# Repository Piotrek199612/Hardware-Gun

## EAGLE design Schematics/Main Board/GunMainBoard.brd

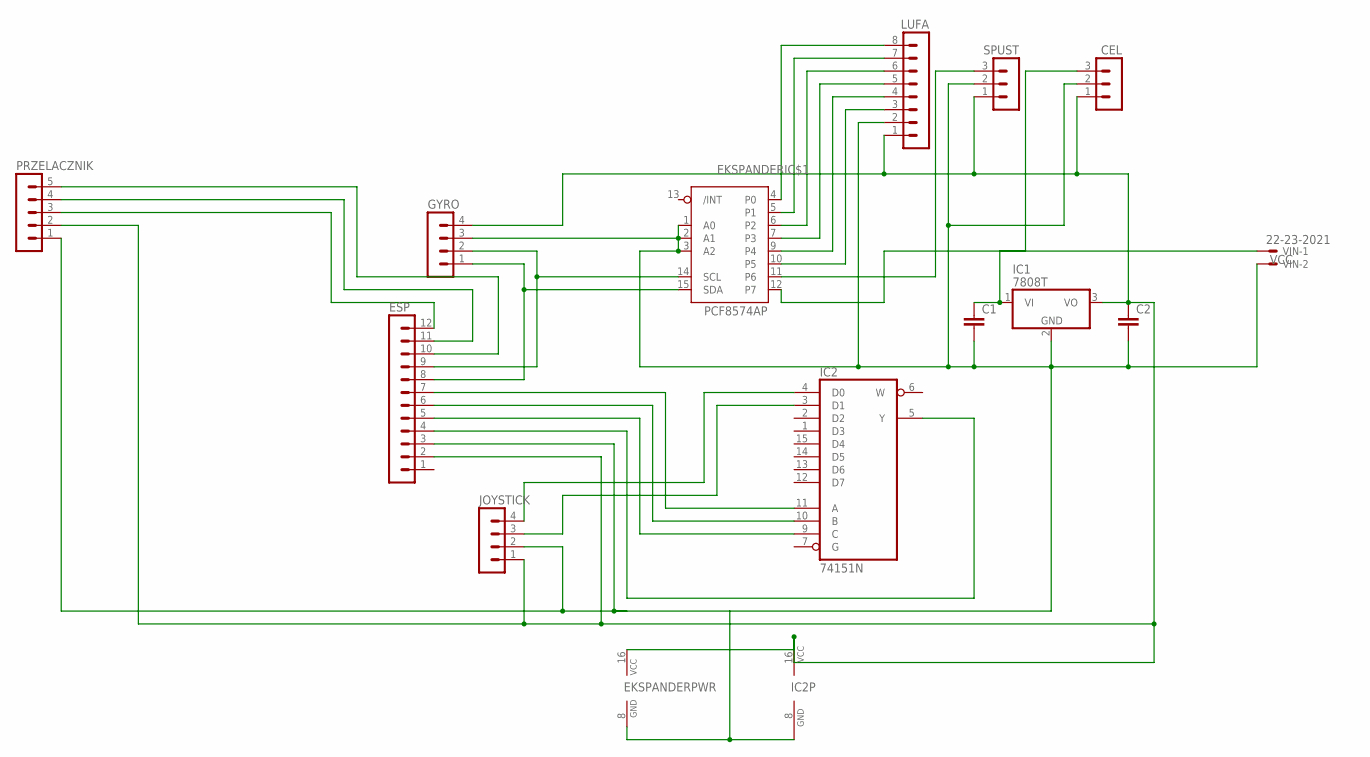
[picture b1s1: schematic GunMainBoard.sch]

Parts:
C1, C2: C-EU025-024X044; C025-024X044
CEL: MA03-1
EKSPANDER: PCF8574AP; DIL16
ESP: MA12-1
GYRO: MA04-1
IC1: 7808T; TO220H
IC2: 74151N; DIL16
JOYSTICK: MA04-1
LUFA: MA08-1
PRZELACZNIK: MA05-1
SPUST: MA03-1
VIN: 22-23-2021

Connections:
unnamed: ESP.10, PRZELACZNIK.5
unnamed: EKSPANDER.15 (SDA), ESP.8, GYRO.1
unnamed: EKSPANDER.4 (P0), LUFA.8
unnamed: ESP.7, IC2.11 (A)
unnamed: EKSPANDER.14 (SCL), ESP.9, GYRO.2
unnamed: ESP.6, IC2.10 (B)
unnamed: ESP.5, IC2.9 (C)
unnamed: ESP.4, IC2.5 (Y)
unnamed: C1.2, C2.2, CEL.2, EKSPANDER.1 (A0), EKSPANDER.2 (A1), EKSPANDER.3 (A2), EKSPANDER.8 (GND), ESP.3, GYRO.3, IC1.2 (GND), IC2.8 (GND), JOYSTICK.2, LUFA.2, PRZELACZNIK.1, SPUST.2, VIN.2
unnamed: EKSPANDER.5 (P1), LUFA.7
unnamed: EKSPANDER.6 (P2), LUFA.6
unnamed: EKSPANDER.7 (P3), LUFA.5
unnamed: EKSPANDER.9 (P4), LUFA.4
unnamed: EKSPANDER.10 (P5), LUFA.3
unnamed: EKSPANDER.11 (P6), SPUST.3
unnamed: C1.1, IC1.1 (VI), VIN.1
unnamed: IC2.3 (D1), JOYSTICK.3
unnamed: CEL.3, EKSPANDER.12 (P7)
unnamed: IC2.4 (D0), JOYSTICK.4
unnamed: ESP.11, PRZELACZNIK.4
unnamed: ESP.12, PRZELACZNIK.3
unnamed: C2.1, CEL.1, EKSPANDER.16 (VCC), ESP.2, GYRO.4, IC1.3 (VO), IC2.16 (VCC), JOYSTICK.1, LUFA.1, PRZELACZNIK.2, SPUST.1

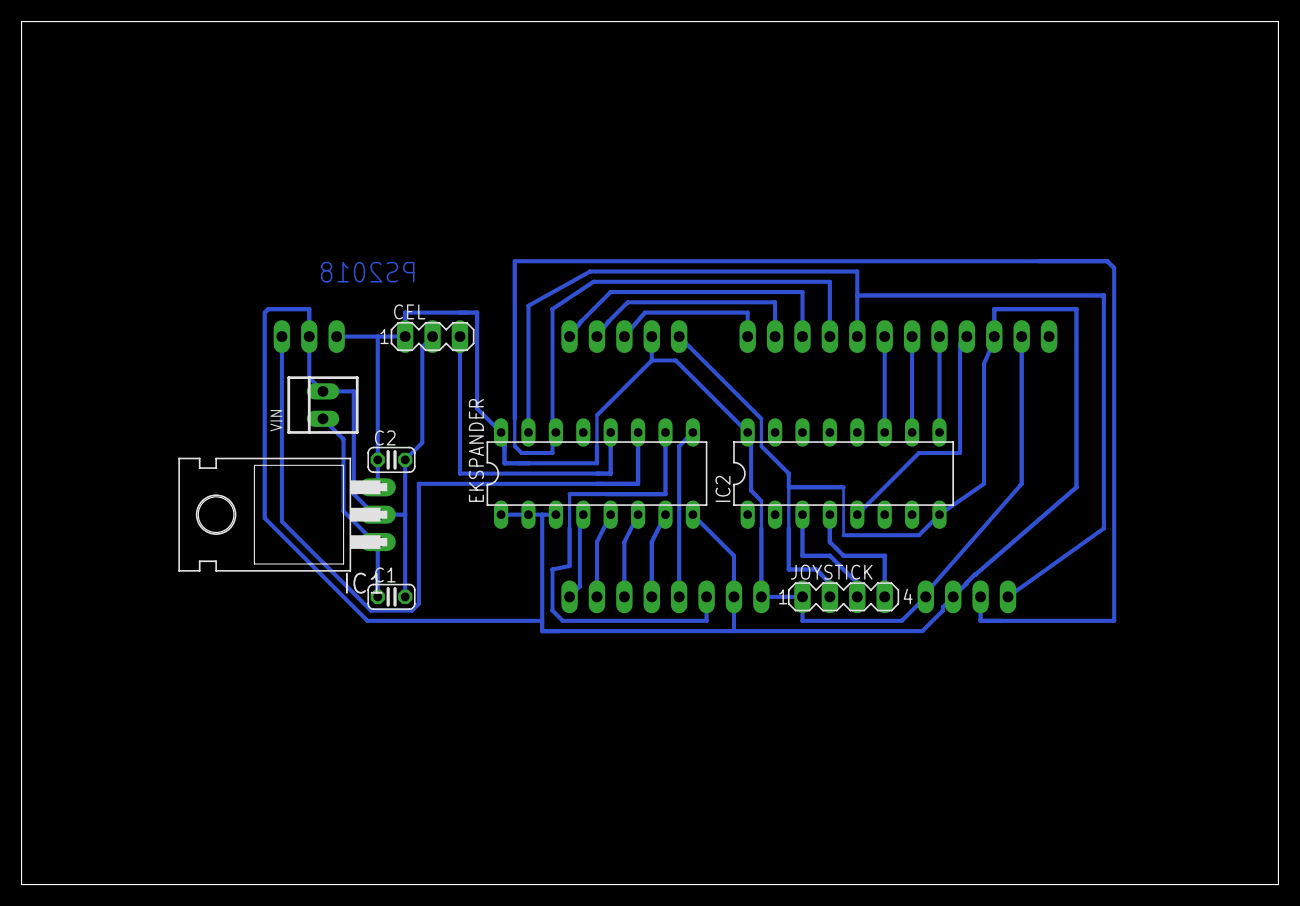
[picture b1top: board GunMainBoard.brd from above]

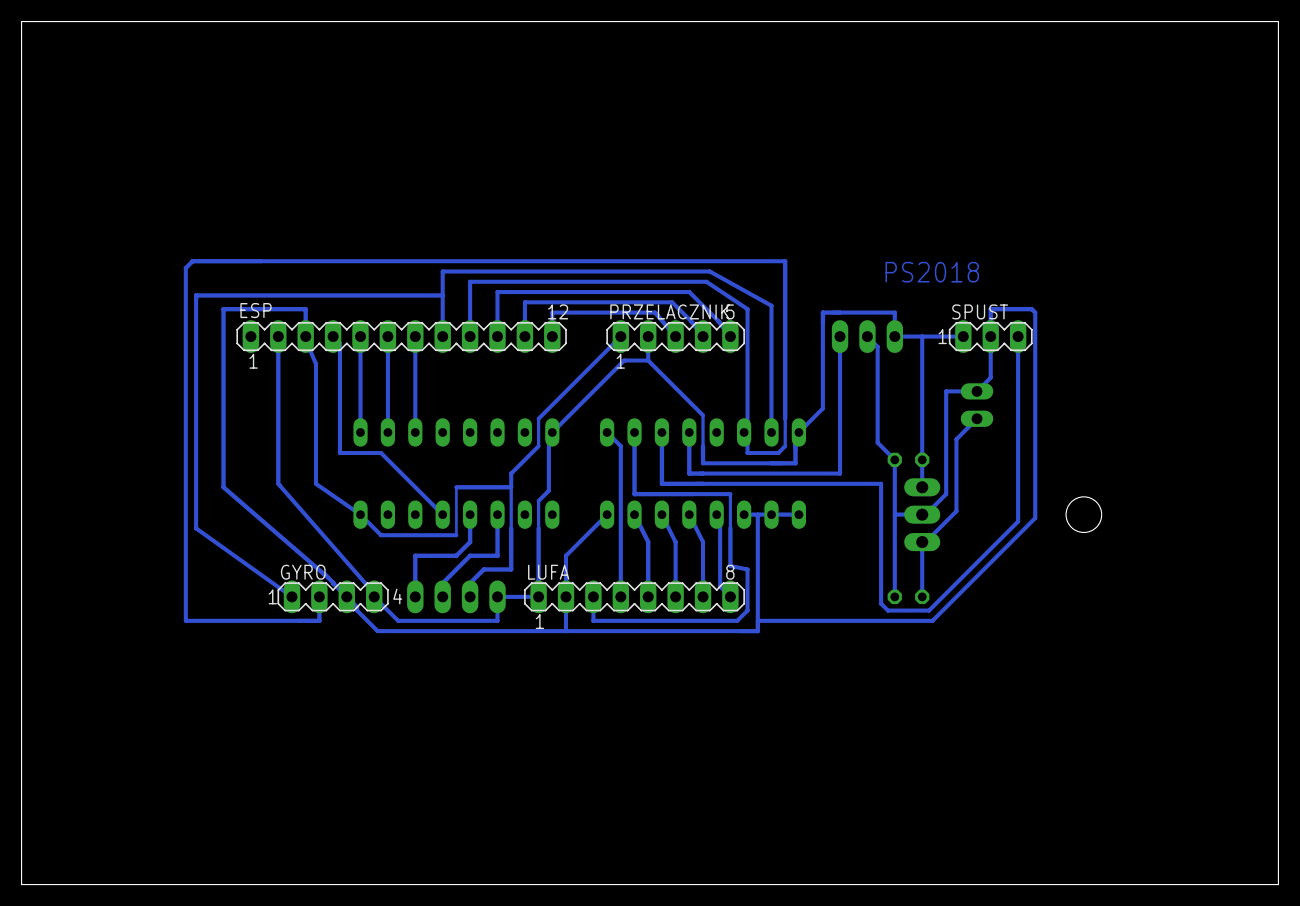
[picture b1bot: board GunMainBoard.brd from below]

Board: 2 copper layers, 116.5 x 80.0 mm, 13 parts (5 on the bottom side), 22 nets.

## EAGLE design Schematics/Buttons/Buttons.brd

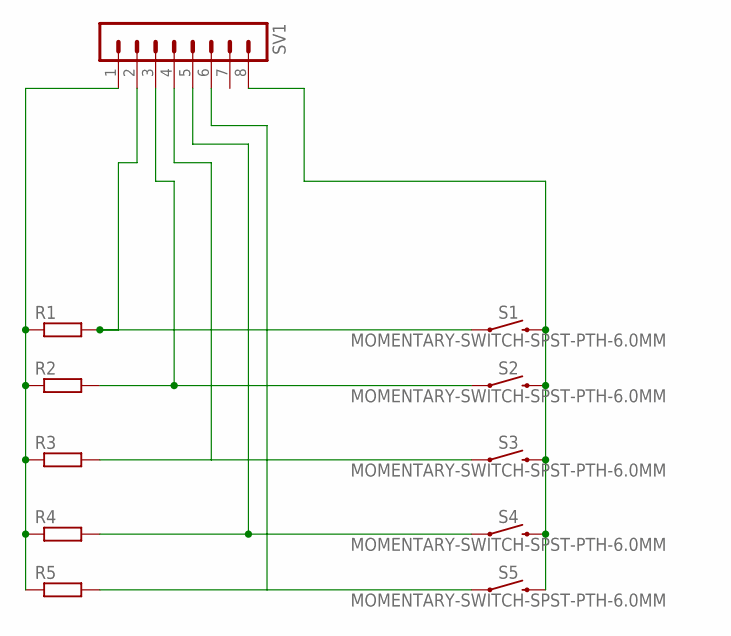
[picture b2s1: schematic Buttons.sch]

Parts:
R1, R2, R3, R4, R5: R0204/7; 0204/7
S1, S2, S3, S4, S5: MOMENTARY-SWITCH-SPST-PTH-6.0MM; TACTILE_SWITCH_PTH_6.0MM
SV1: MA08-1

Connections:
unnamed: R1.2, S1.1, SV1.2
unnamed: R2.2, S2.1, SV1.3
unnamed: R3.2, S3.1, SV1.4
unnamed: R4.2, S4.1, SV1.5
unnamed: R5.2, S5.1, SV1.6
unnamed: R1.1, R2.1, R3.1, R4.1, R5.1, SV1.1
unnamed: S1.3 (2), S2.3 (2), S3.3 (2), S4.3 (2), S5.3 (2), SV1.8

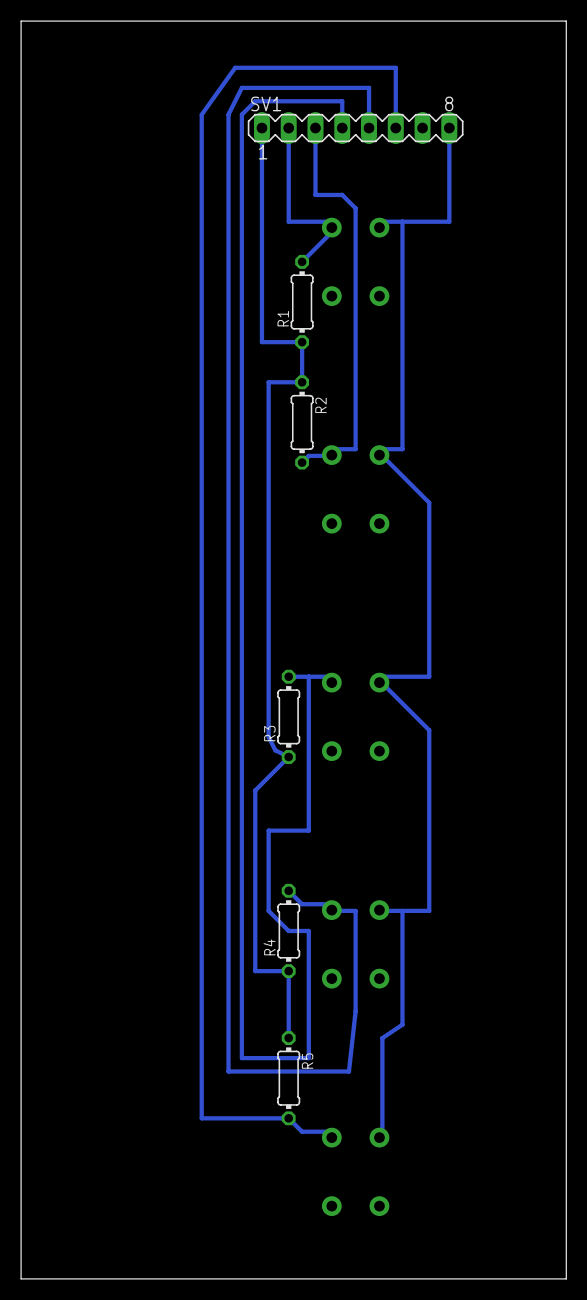
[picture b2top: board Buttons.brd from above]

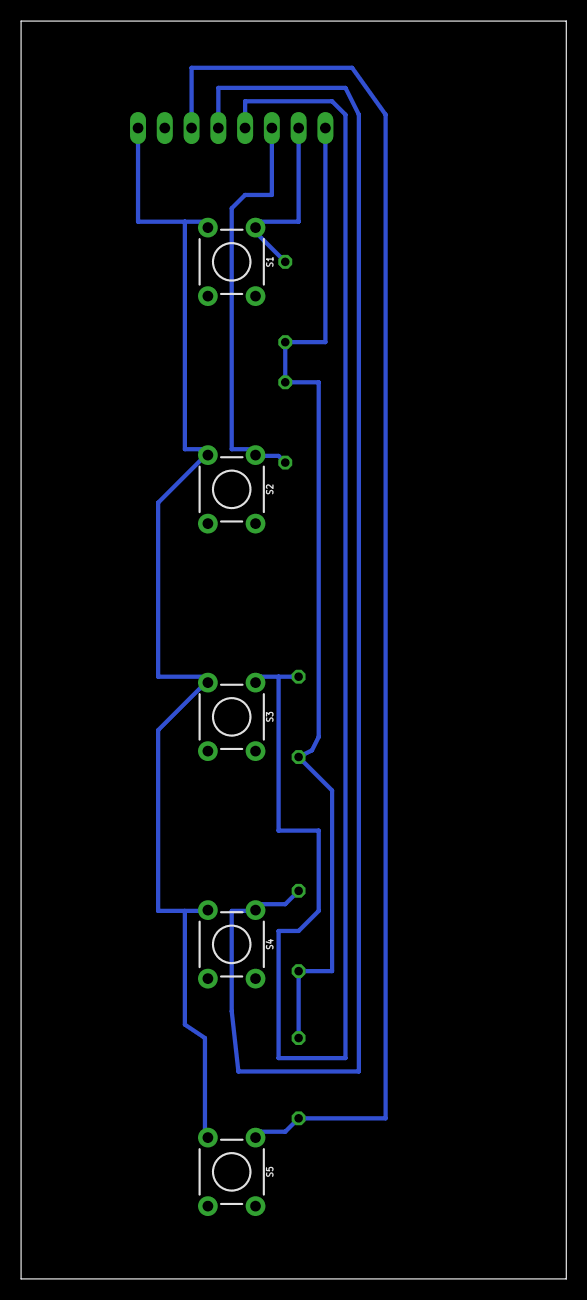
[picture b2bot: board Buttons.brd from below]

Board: 2 copper layers, 51.7 x 119.4 mm, 11 parts (5 on the bottom side), 7 nets.

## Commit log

2018-02-18 Schematics.
2018-02-18 Recive messages and keyboard handling.
2018-02-24 Gui and key mapping added.
2018-03-04 Accelerometer Y axis movement.
2018-03-18 Madgwick filter

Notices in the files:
parts and their libraries:
SparkFun-Switches: Licensing: Creative Commons ShareAlike 4.0 International - https://creativecommons.org/licenses/by-sa/4.0
